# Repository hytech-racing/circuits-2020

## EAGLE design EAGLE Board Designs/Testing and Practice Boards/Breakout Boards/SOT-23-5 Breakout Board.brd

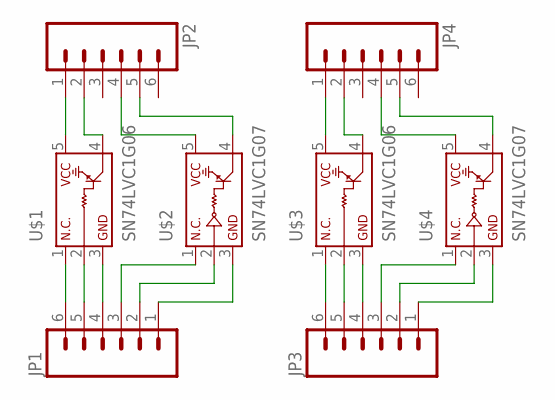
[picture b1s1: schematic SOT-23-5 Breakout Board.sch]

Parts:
JP1, JP2, JP3, JP4: M06; 1X06
U$1, U$3: SN74LVC1G06; SOT-23-5
U$2, U$4: SN74LVC1G07; SOT-23-5

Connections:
unnamed: JP2.1, U$1.5
unnamed: JP2.2, U$1.4
unnamed: JP2.4, U$2.5
unnamed: JP2.5, U$2.4
unnamed: JP1.6, U$1.1
unnamed: JP1.5, U$1.2
unnamed: JP1.4, U$1.3
unnamed: JP1.3, U$2.1
unnamed: JP1.2, U$2.2
unnamed: JP1.1, U$2.3
unnamed: JP4.1, U$3.5
unnamed: JP4.2, U$3.4
unnamed: JP4.4, U$4.5
unnamed: JP4.5, U$4.4
unnamed: JP3.6, U$3.1
unnamed: JP3.5, U$3.2
unnamed: JP3.4, U$3.3
unnamed: JP3.3, U$4.1
unnamed: JP3.2, U$4.2
unnamed: JP3.1, U$4.3

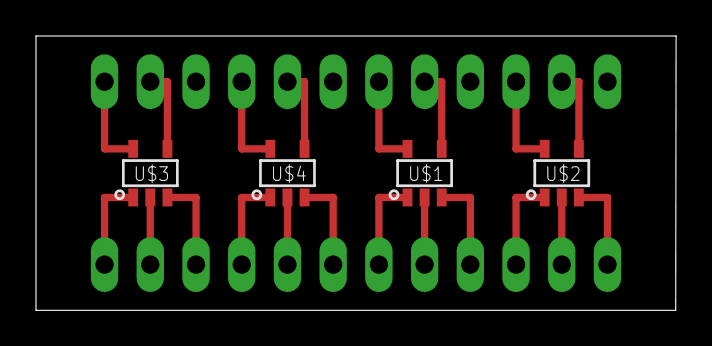
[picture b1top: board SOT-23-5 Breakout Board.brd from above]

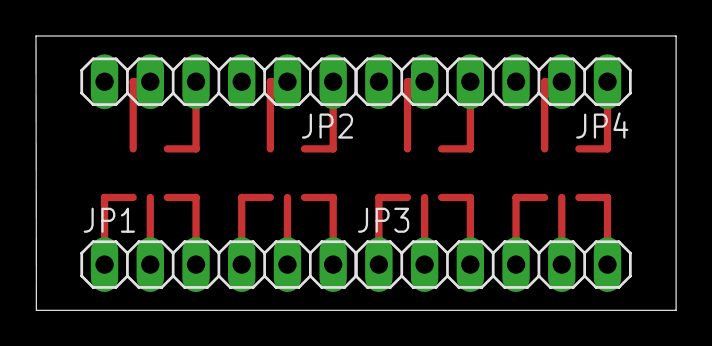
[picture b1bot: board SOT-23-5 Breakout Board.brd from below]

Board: 2 copper layers, 35.6 x 15.2 mm, 8 parts (4 on the bottom side), 20 nets.

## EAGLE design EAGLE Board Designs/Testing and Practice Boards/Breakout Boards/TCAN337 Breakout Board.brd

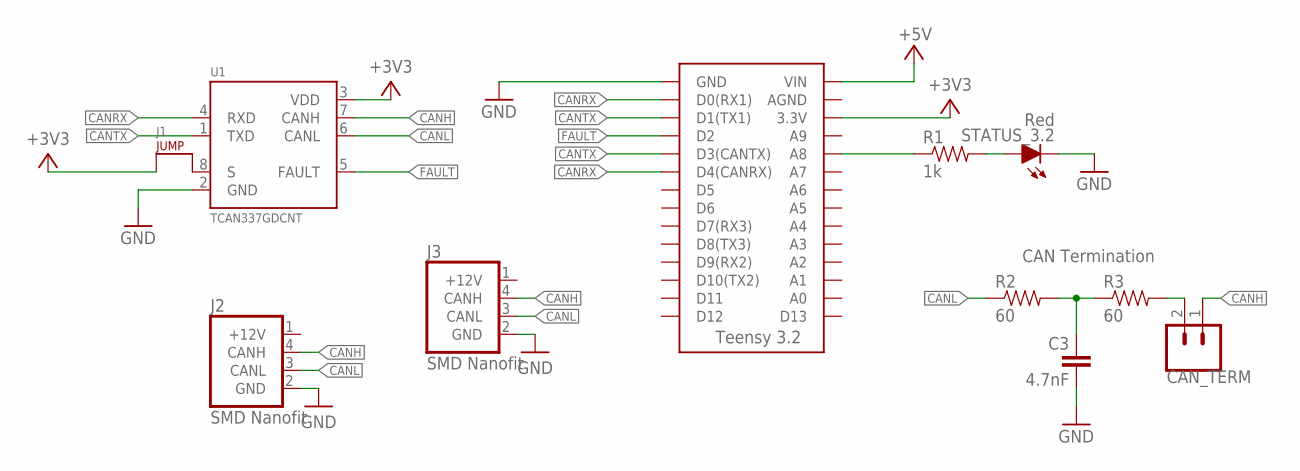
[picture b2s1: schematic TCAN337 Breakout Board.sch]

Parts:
3.2: TEENSY_3.2_SIMPLE
C3: 4.7nF; 0603-CAP
CAN_TERM: M02_SLIM; 1X02_SLIM
J1: JUMPER.1; 1X02
J2, J3: CONNECTOR-CAN; MOLEX_NANOFIT_SMD_04
R1: 1k; 0603-RES
R2, R3: 60; 0603-RES
STATUS_3.2: Red; LED-603
U1: CAN_TRANSCIEVER_TCAN337TCAN337SOT-23-8; SOT-23-8

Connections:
+3V3: 3.2.3.3V, J1.1, U1.3 (VDD)
+5V: 3.2.VIN
+12V: J2.1 (+12V), J3.1 (+12V)
CANH: CAN_TERM.1, J2.4 (CANH), J3.4 (CANH), U1.7 (CANH)
CANL: J2.3 (CANL), J3.3 (CANL), R2.1, U1.6 (CANL)
CANRX: 3.2.D0(RX1), 3.2.D4(CANRX), U1.4 (RXD)
CANTX: 3.2.D1(TX1), 3.2.D3(CANTX), U1.1 (TXD)
FAULT: 3.2.D2, U1.5 (FAULT)
GND: 3.2.GND, C3.2, J2.2 (GND), J3.2 (GND), STATUS_3.2.C, U1.2 (GND)
unnamed: J1.2, U1.8 (S)
unnamed: C3.1, R2.2, R3.1
unnamed: 3.2.A8, R1.1
unnamed: R1.2, STATUS_3.2.A
unnamed: CAN_TERM.2, R3.2

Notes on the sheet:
CAN Termination

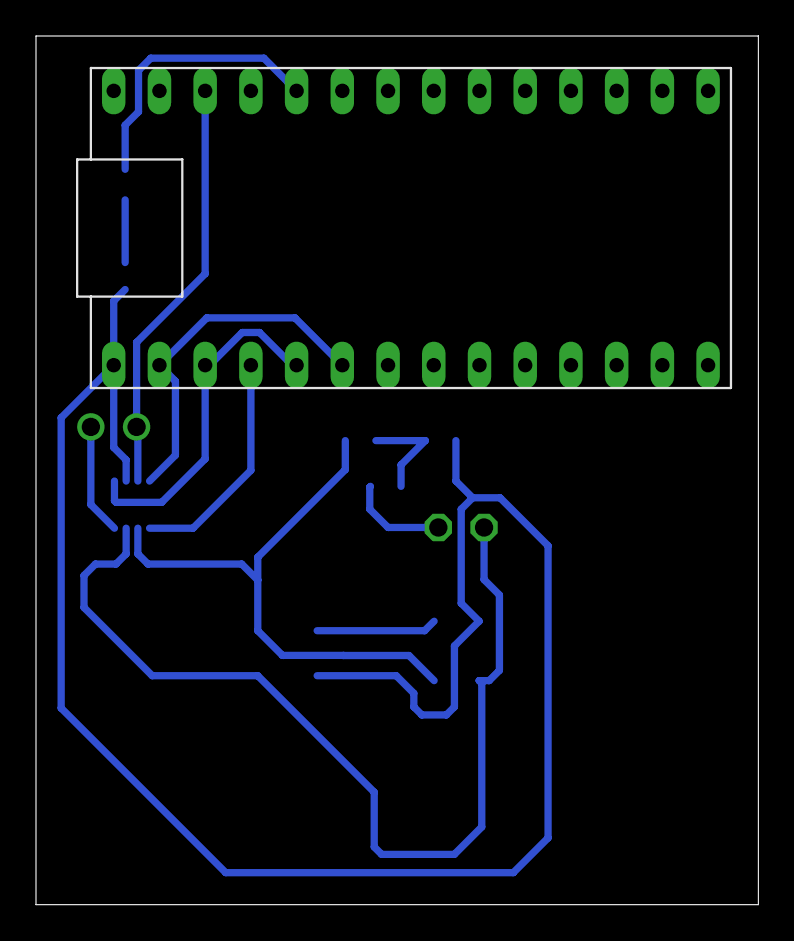
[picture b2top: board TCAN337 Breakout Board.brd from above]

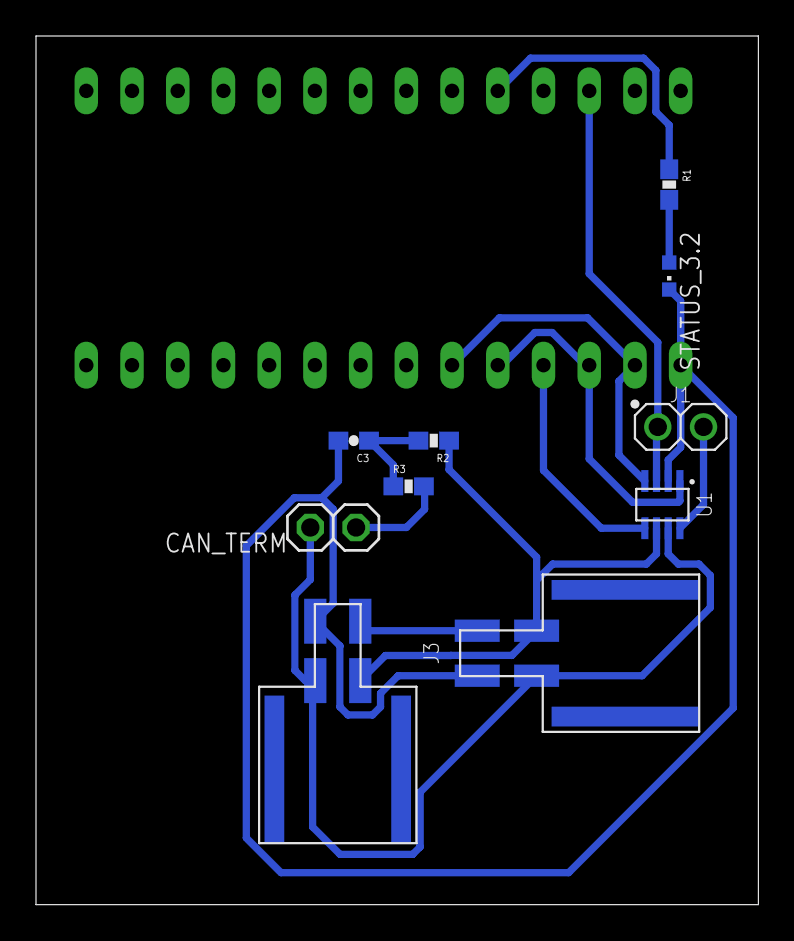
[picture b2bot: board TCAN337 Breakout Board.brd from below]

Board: 2 copper layers, 40.1 x 48.3 mm, 11 parts (10 on the bottom side), 13 nets.

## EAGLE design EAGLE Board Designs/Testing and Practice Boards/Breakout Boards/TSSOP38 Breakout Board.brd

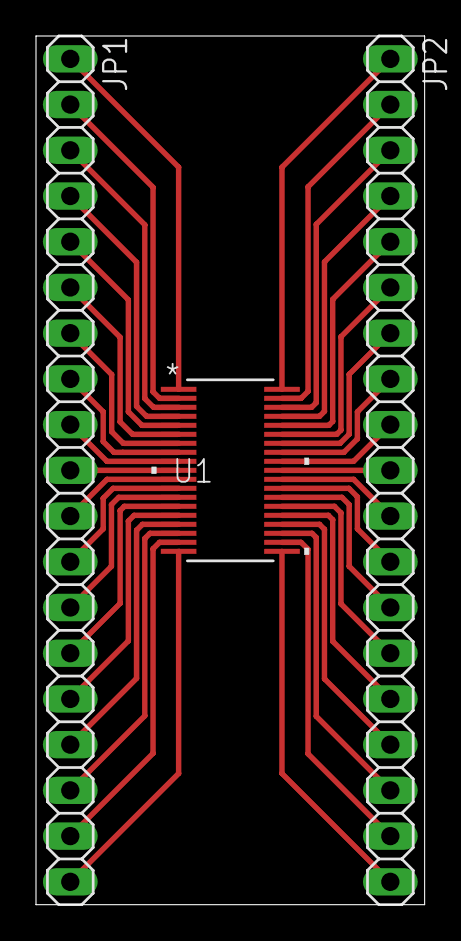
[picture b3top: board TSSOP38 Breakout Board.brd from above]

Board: 2 copper layers, 21.6 x 48.3 mm, 3 parts (0 on the bottom side), 38 nets.

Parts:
JP1, JP2: 1X19
U1: ADS7952SDBTDBT38-M; DBT38-M

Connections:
unnamed: JP1.1, U1.1
unnamed: JP1.2, U1.2
unnamed: JP1.3, U1.3
unnamed: JP1.4, U1.4
unnamed: JP1.5, U1.5
unnamed: JP1.6, U1.6
unnamed: JP1.7, U1.7
unnamed: JP1.8, U1.8
unnamed: JP1.19, U1.19
unnamed: JP1.18, U1.18
unnamed: JP1.17, U1.17
unnamed: JP1.16, U1.16
unnamed: JP1.15, U1.15
unnamed: JP1.14, U1.14
unnamed: JP1.13, U1.13
unnamed: JP1.12, U1.12
unnamed: JP1.11, U1.11
unnamed: JP1.10, U1.10
unnamed: JP1.9, U1.9
unnamed: JP2.1, U1.38
unnamed: JP2.2, U1.37
unnamed: JP2.3, U1.36
unnamed: JP2.4, U1.35
unnamed: JP2.5, U1.34
unnamed: JP2.6, U1.33
unnamed: JP2.7, U1.32
unnamed: JP2.8, U1.31
unnamed: JP2.9, U1.30
unnamed: JP2.10, U1.29
unnamed: JP2.11, U1.28
unnamed: JP2.12, U1.27
unnamed: JP2.13, U1.26
unnamed: JP2.14, U1.25
unnamed: JP2.15, U1.24
unnamed: JP2.16, U1.23
unnamed: JP2.17, U1.22
unnamed: JP2.18, U1.21
unnamed: JP2.19, U1.20

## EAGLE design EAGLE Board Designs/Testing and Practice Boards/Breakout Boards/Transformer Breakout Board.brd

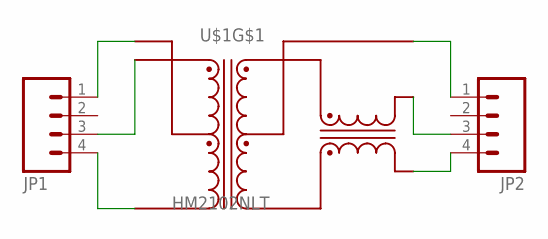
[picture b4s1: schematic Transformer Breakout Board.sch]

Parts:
JP1, JP2: M04; 1X04
U$1: HM2102NLT

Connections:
unnamed: JP1.1, U$1.P$2 (MCT)
unnamed: JP1.3, U$1.P$1 (MX+)
unnamed: JP1.4, U$1.P$3 (MX-)
unnamed: JP2.4, U$1.P$10 (TD-)
unnamed: JP2.3, U$1.P$12 (TD+)
unnamed: JP2.1, U$1.P$11 (TCT)

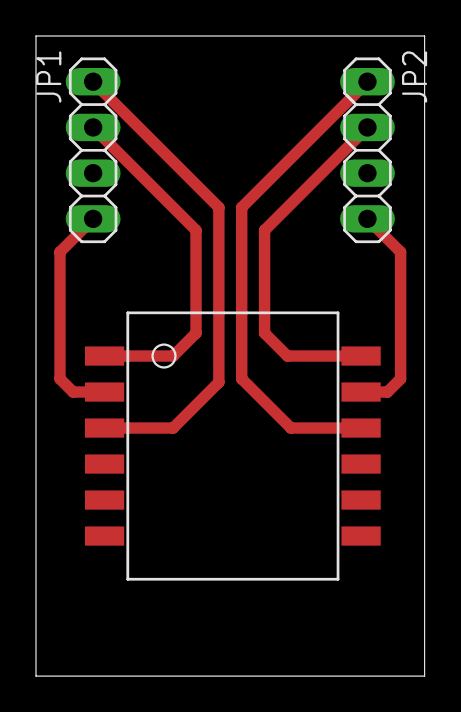
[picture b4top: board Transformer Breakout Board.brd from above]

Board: 2 copper layers, 21.6 x 35.6 mm, 3 parts (0 on the bottom side), 6 nets.

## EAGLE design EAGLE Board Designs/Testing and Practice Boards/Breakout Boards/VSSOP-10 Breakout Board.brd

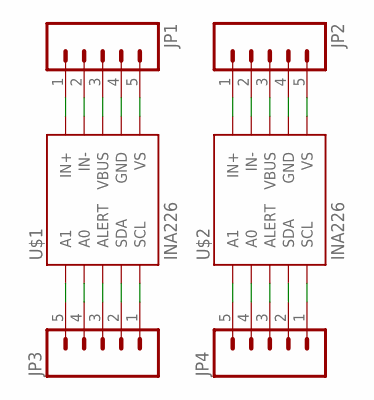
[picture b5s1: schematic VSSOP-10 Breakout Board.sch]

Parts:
JP1, JP2, JP3, JP4: M05; 1X05
U$1, U$2: INA226; VSSOP-10

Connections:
unnamed: JP4.1, U$2.5 (SCL)
unnamed: JP4.2, U$2.4 (SDA)
unnamed: JP4.3, U$2.3 (ALERT)
unnamed: JP4.4, U$2.2 (A0)
unnamed: JP4.5, U$2.1 (A1)
unnamed: JP3.1, U$1.5 (SCL)
unnamed: JP3.2, U$1.4 (SDA)
unnamed: JP3.3, U$1.3 (ALERT)
unnamed: JP3.4, U$1.2 (A0)
unnamed: JP3.5, U$1.1 (A1)
unnamed: JP2.1, U$2.10 (IN+)
unnamed: JP2.2, U$2.9 (IN-)
unnamed: JP2.3, U$2.8 (VBUS)
unnamed: JP2.4, U$2.7 (GND)
unnamed: JP2.5, U$2.6 (VS)
unnamed: JP1.1, U$1.10 (IN+)
unnamed: JP1.2, U$1.9 (IN-)
unnamed: JP1.3, U$1.8 (VBUS)
unnamed: JP1.4, U$1.7 (GND)
unnamed: JP1.5, U$1.6 (VS)

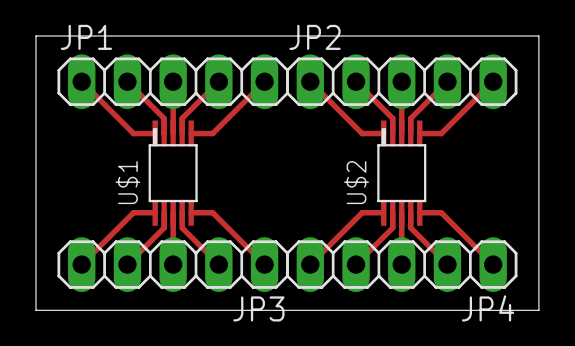
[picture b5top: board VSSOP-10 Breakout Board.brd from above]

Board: 2 copper layers, 27.9 x 15.2 mm, 6 parts (0 on the bottom side), 20 nets.

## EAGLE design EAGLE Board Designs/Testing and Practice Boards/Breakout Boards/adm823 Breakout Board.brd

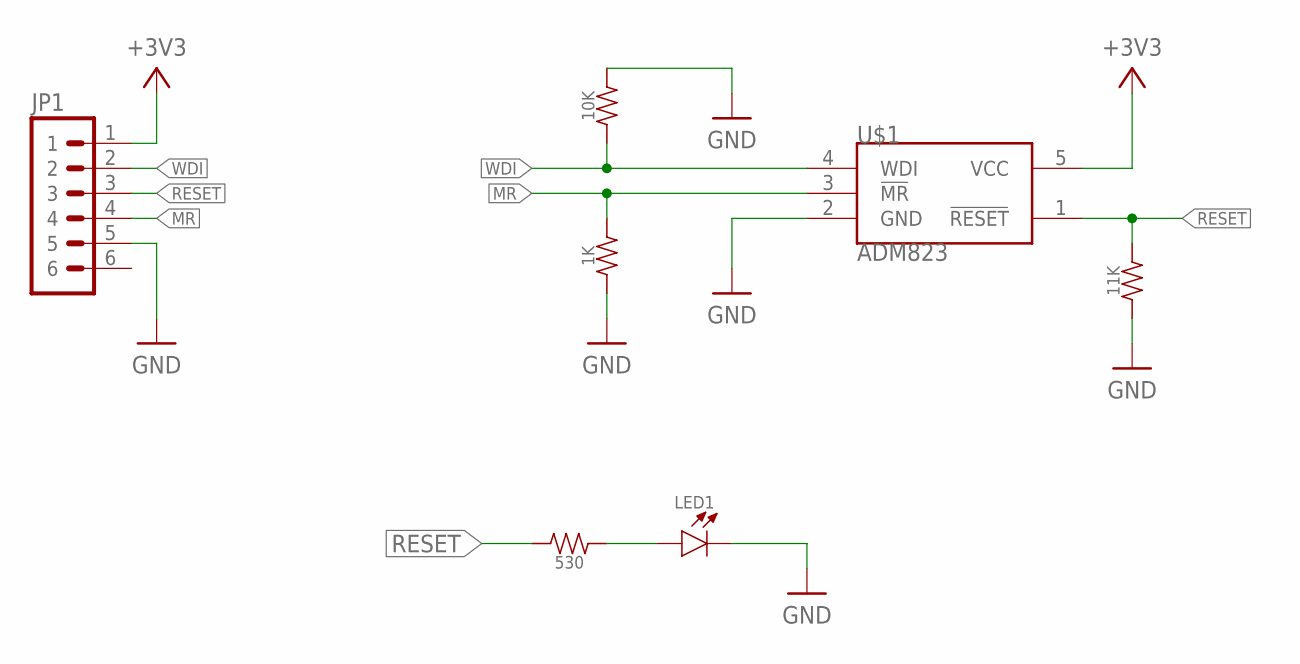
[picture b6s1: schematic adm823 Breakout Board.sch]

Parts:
1K, 530: RESISTOR_0603_; 0603-RES
10K, 11K: 10k; 0603-RES
JP1: M06; 1X06
LED1: LED-0603; LED-603
U$1: ADM823; SOT323-5

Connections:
+3V3: JP1.1, U$1.5 (VCC)
GND: 1K.1, 10K.2, 11K.1, JP1.5, LED1.C, U$1.2 (GND)
MR: 1K.2, JP1.4, U$1.3 (!MR!)
unnamed: 530.1, LED1.A
RESET: 11K.2, 530.2, JP1.3, U$1.1 (!RESET!)
WDI: 10K.1, JP1.2, U$1.4 (WDI)

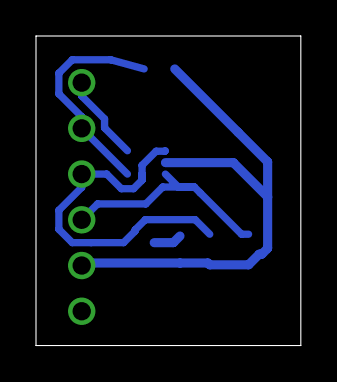
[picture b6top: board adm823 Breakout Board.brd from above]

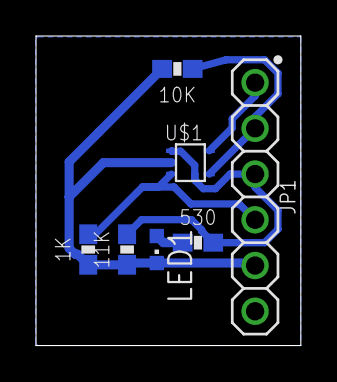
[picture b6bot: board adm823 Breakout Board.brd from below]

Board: 1 copper layer, 14.7 x 17.2 mm, 7 parts (7 on the bottom side), 6 nets.

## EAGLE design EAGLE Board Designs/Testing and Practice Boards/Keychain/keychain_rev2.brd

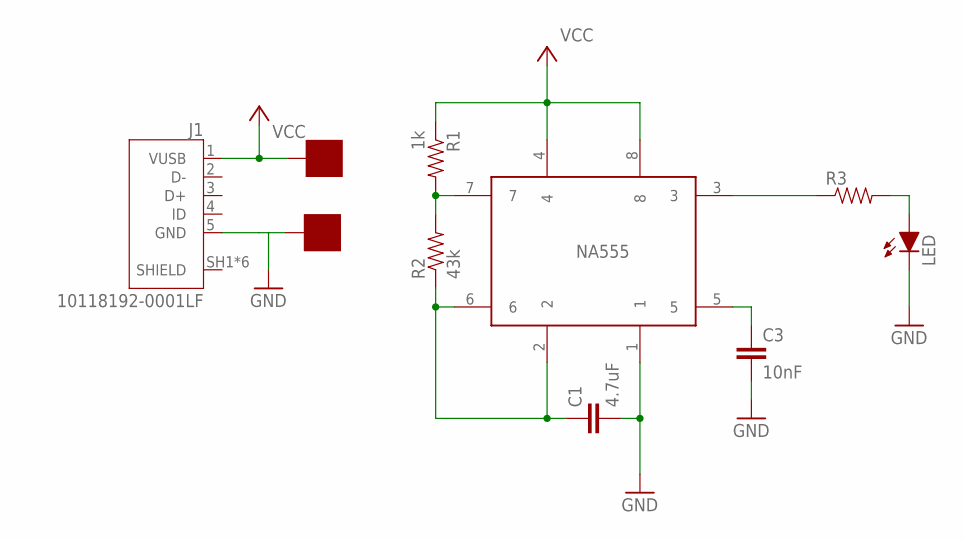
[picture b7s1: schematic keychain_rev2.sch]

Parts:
5V: SOLDER_PAD; SOLDER_PAD_XSMALL
C1: 4.7uF; 0603-CAP; TOLERANCE 5%; VOLTAGE 25V
C3: 10nF; 0603-CAP; TOLERANCE 5%; VOLTAGE 25V
GND: SOLDER_PAD; SOLDER_PAD_XSMALL
J1: 10118192-0001LF; AMPHENOL_10118192-0001LF
LED: LED-0603; LED-603
NA555: NA555SO-8; SOIC-08
R1: 1k; 0603-RES; TOLERANCE 1%
R2: 43k; 0603-RES; TOLERANCE 1%
R3: RESISTOR0603; 0603-RES

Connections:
GND: C1.2, C3.2, GND.P$1, J1.5 (GND), LED.C, NA555.1
unnamed: LED.A, R3.2
unnamed: C1.1, NA555.2, NA555.6, R2.1
unnamed: NA555.7, R1.2, R2.2
unnamed: C3.1, NA555.5
RED: NA555.3, R3.1
VCC: 5V.P$1, J1.1 (VUSB), NA555.4, NA555.8, R1.1

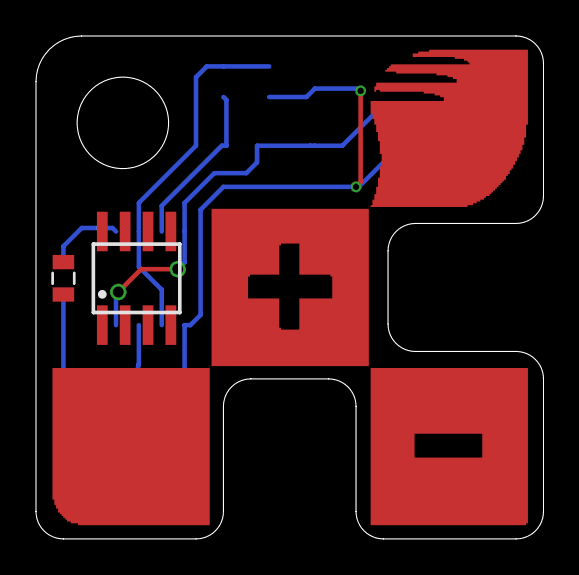
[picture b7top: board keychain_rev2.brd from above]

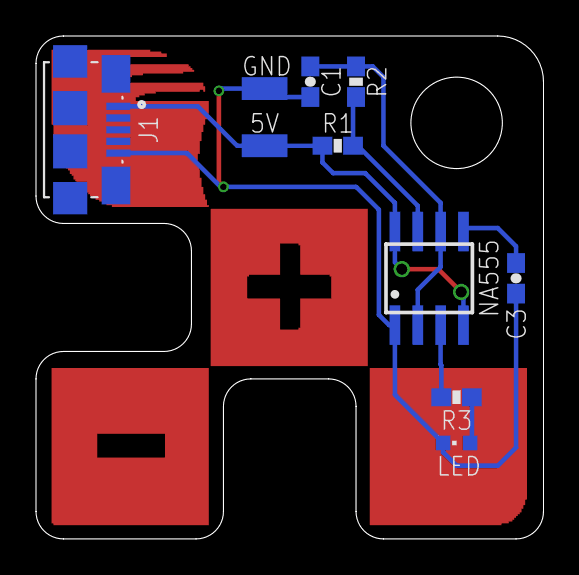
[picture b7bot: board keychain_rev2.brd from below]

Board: 2 copper layers, 28.2 x 27.9 mm, 12 parts (10 on the bottom side), 7 nets.

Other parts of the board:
E$1: 0805@1
E$2: SOIC-08
